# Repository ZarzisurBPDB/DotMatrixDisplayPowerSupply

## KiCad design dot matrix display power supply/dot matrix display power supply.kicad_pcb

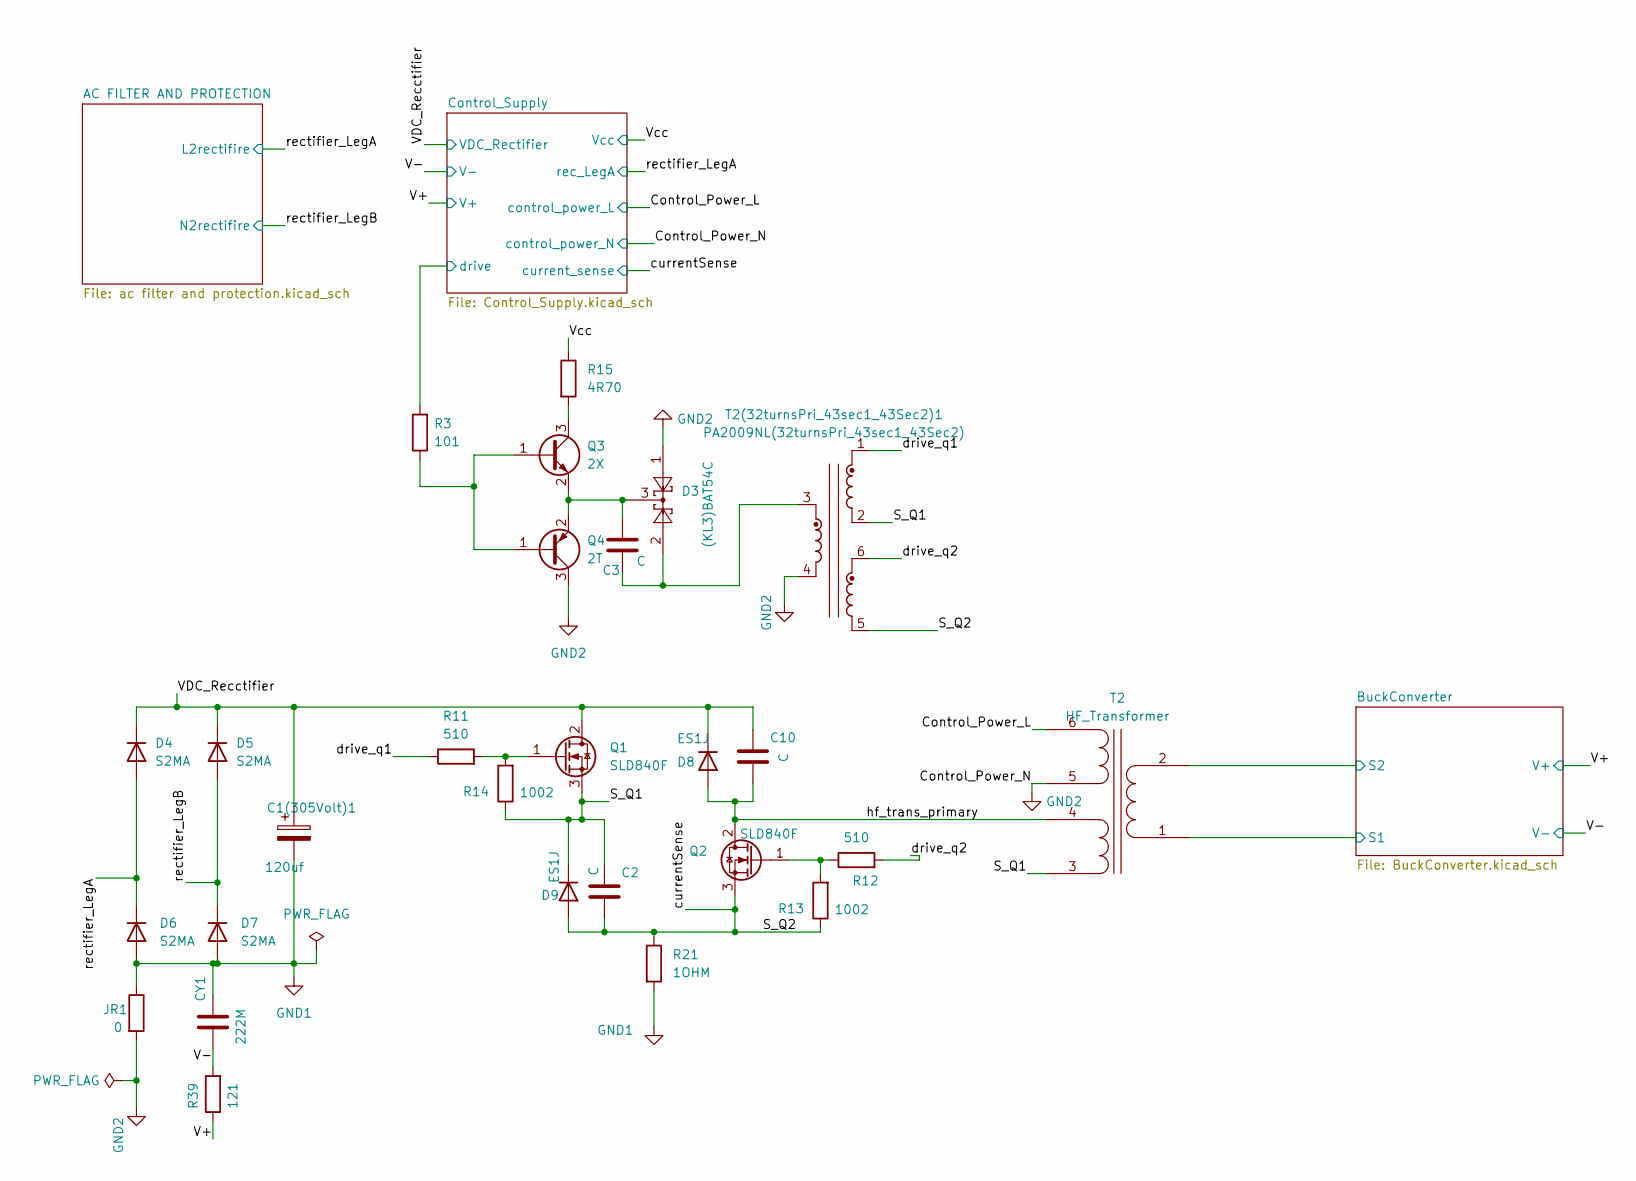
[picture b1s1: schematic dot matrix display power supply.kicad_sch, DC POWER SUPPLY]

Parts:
C1(305Volt)1: 120uf; CP_Radial_D16.0mm_P7.50mm
C2, C10: C; C_Disc_D4.7mm_W2.5mm_P5.00mm
C3: C; C_0201_0603Metric
CY1: 222M; C_Axial_L3.8mm_D2.6mm_P7.50mm_Horizontal
D3: (KL3)BAT54C; SOT-23
D4, D5, D6, D7: S2MA; D_SMA
D8, D9: ES1J; D_SMA
JR1: 0; R_0603_1608Metric
Q1, Q2: SLD840F; TO-252-2
Q3: 2X; SOT-23
Q4: 2T; SOT-23
R3: 101; R_0402_1005Metric
R11: 510; R_0402_1005Metric
R12: 510; R_0603_1608Metric
R13: 1002; R_0603_1608Metric
R14: 1002; R_0402_1005Metric
R15: 4R70; R_0603_1608Metric
R21: 1OHM; R_Axial_DIN0414_L11.9mm_D4.5mm_P15.24mm_Horizontal
R39: 121; R_0402_1005Metric
T2: HF_Transformer
T2(32turnsPri_43sec1_43Sec2)1: PA2009NL(32turnsPri_43sec1_43Sec2); Pulse_PA2004NL

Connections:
/BuckConverter/s1: T2.2 (s2); also elsewhere on the board
/BuckConverter/s2: T2.1 (s1); also elsewhere on the board
/Control_Power_L: T2.6 (controlPWR2); also elsewhere on the board
/Control_Supply/drive: R3.2; also elsewhere on the board
/S_Q1: C2.1, D9.1 (K), Q1.3 (S), R14.1, T2.3 (p1), T2(32turnsPri_43sec1_43Sec2)1.2
/S_Q2: C2.2, D9.2 (A), Q2.3 (S), R13.1, R21.1, T2(32turnsPri_43sec1_43Sec2)1.5; also elsewhere on the board
/V+: R39.1; also elsewhere on the board
/V-: CY1.2, R39.2; also elsewhere on the board
/VDC_Recctifier: C1(305Volt)1.1, C10.1, D4.1 (K), D5.1 (K), D8.1 (K), Q1.2 (D); also elsewhere on the board
/Vcc: R15.1; also elsewhere on the board
/drive_q1: R11.1, T2(32turnsPri_43sec1_43Sec2)1.1
/drive_q2: R12.2, T2(32turnsPri_43sec1_43Sec2)1.6
/hf_trans_primary: C10.2, D8.2 (A), Q2.2 (D), T2.4 (p2)
/rectifier_LegA: D4.2 (A), D6.1 (K); also elsewhere on the board
/rectifier_LegB: D5.2 (A), D7.1 (K); also elsewhere on the board
GND1: C1(305Volt)1.2, CY1.1, D6.2 (A), D7.2 (A), JR1.1, R21.2; also elsewhere on the board
GND2: D3.1, JR1.2, Q4.3 (C), T2.5 (ControlPWR1), T2(32turnsPri_43sec1_43Sec2)1.4; also elsewhere on the board
unnamed: C3.1, D3.2, T2(32turnsPri_43sec1_43Sec2)1.3
unnamed: Q1.1 (G), R11.2, R14.2
unnamed: Q2.1 (G), R12.1, R13.2
unnamed: Q3.1 (B), Q4.1 (B), R3.1
unnamed: Q3.3 (C), R15.2
unnamed: C3.2, D3.3, Q3.2 (E), Q4.2 (E)

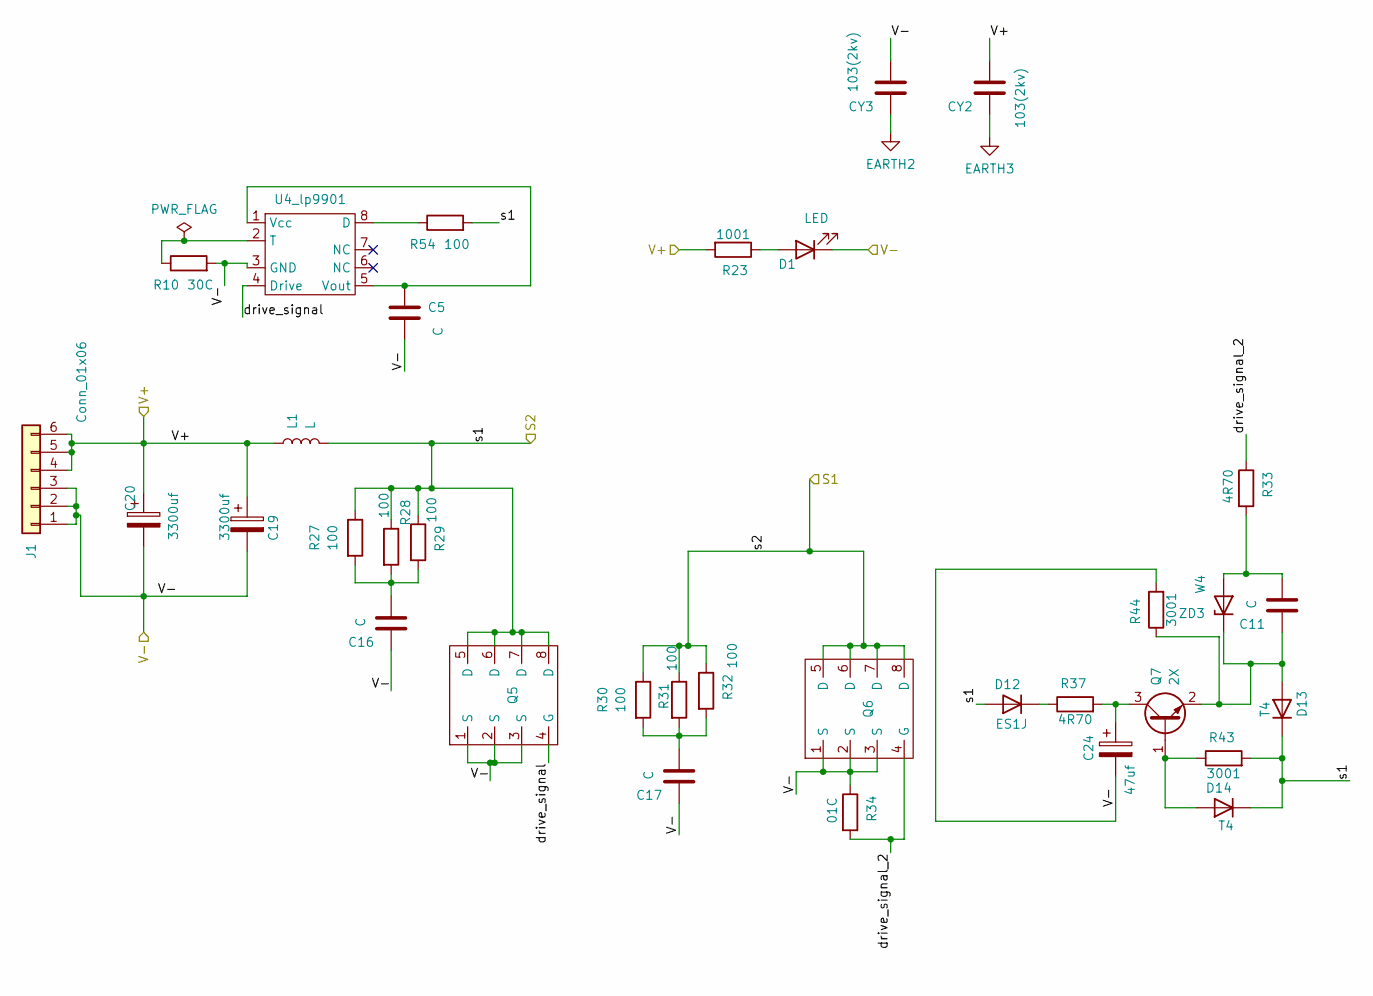
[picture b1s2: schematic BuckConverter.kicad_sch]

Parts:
C5, C11, C16, C17: C; C_01005_0402Metric
C19, C20: 3300uf; CP_Radial_D8.0mm_P5.00mm
C24: 47uf; CP_Radial_D5.0mm_P2.50mm
CY2, CY3: 103(2kv); C_Axial_L3.8mm_D2.6mm_P7.50mm_Horizontal
D1: LED; LED_D5.0mm
D12: ES1J; D_SMA
D13, D14: T4; D_SMA
J1: Conn_01x06; TerminalBlock_MaiXu_MX126-5.0-06P_1x06_P5.00mm
L1: L; L_Toroid_Horizontal_D22.4mm_P19.80mm_Vishay_TJ4
Q5, Q6: BSC022N03S
Q7: 2X; SOT-23
R10: 30C; R_0402_1005Metric
R23: 1001; R_0402_1005Metric
R27, R28, R29, R30, R31, R32, R54: 100; R_0402_1005Metric
R33, R37: 4R70; R_0402_1005Metric
R34: 01C; R_0402_1005Metric
R43, R44: 3001; R_0402_1005Metric
U4_lp9901: lp9901
ZD3: W4; D_SOD-523

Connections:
/BuckConverter/drive_signal: Q5.4 (G), U4_lp9901.4 (Drive)
/BuckConverter/drive_signal_2: Q6.4 (G), R33.1, R34.2
/BuckConverter/s1: D12.2 (A), D13.1 (K), D14.1 (K), L1.2, Q5.5 (D), Q5.6 (D), Q5.7 (D), Q5.8 (D), R27.1, R28.1, R29.1, R43.2, R54.2; also elsewhere on the board
/BuckConverter/s2: Q6.5 (D), Q6.6 (D), Q6.7 (D), Q6.8 (D), R30.1, R31.1, R32.1; also elsewhere on the board
/V+: C19.1, C20.1, CY2.2, J1.4, J1.5, J1.6, L1.1, R23.2; also elsewhere on the board
/V-: C5.1, C16.1, C17.1, C19.2, C20.2, C24.2, CY3.2, D1.1 (K), J1.1, J1.2, J1.3, Q5.1 (S), Q5.2 (S), Q5.3 (S), Q6.1 (S), Q6.2 (S), Q6.3 (S), R10.2, R34.1, R44.2, U4_lp9901.3 (GND); also elsewhere on the board
EARTH2: CY3.1
EARTH3: CY2.1
unnamed: C16.2, R27.2, R28.2, R29.2
unnamed: C17.2, R30.2, R31.2, R32.2
unnamed: D1.2 (A), R23.1
unnamed: D12.1 (K), R37.1
unnamed: C11.1, D13.2 (A), Q7.2 (E), R44.1, ZD3.1 (K)
unnamed: D14.2 (A), Q7.1 (B), R43.1
unnamed: C24.1, Q7.3 (C), R37.2
unnamed: R54.1, U4_lp9901.8 (D)
unnamed: R10.1, U4_lp9901.2 (T)
unnamed: C5.2, U4_lp9901.1 (Vcc), U4_lp9901.5 (Vout)
unnamed: C11.2, R33.2, ZD3.2 (A)

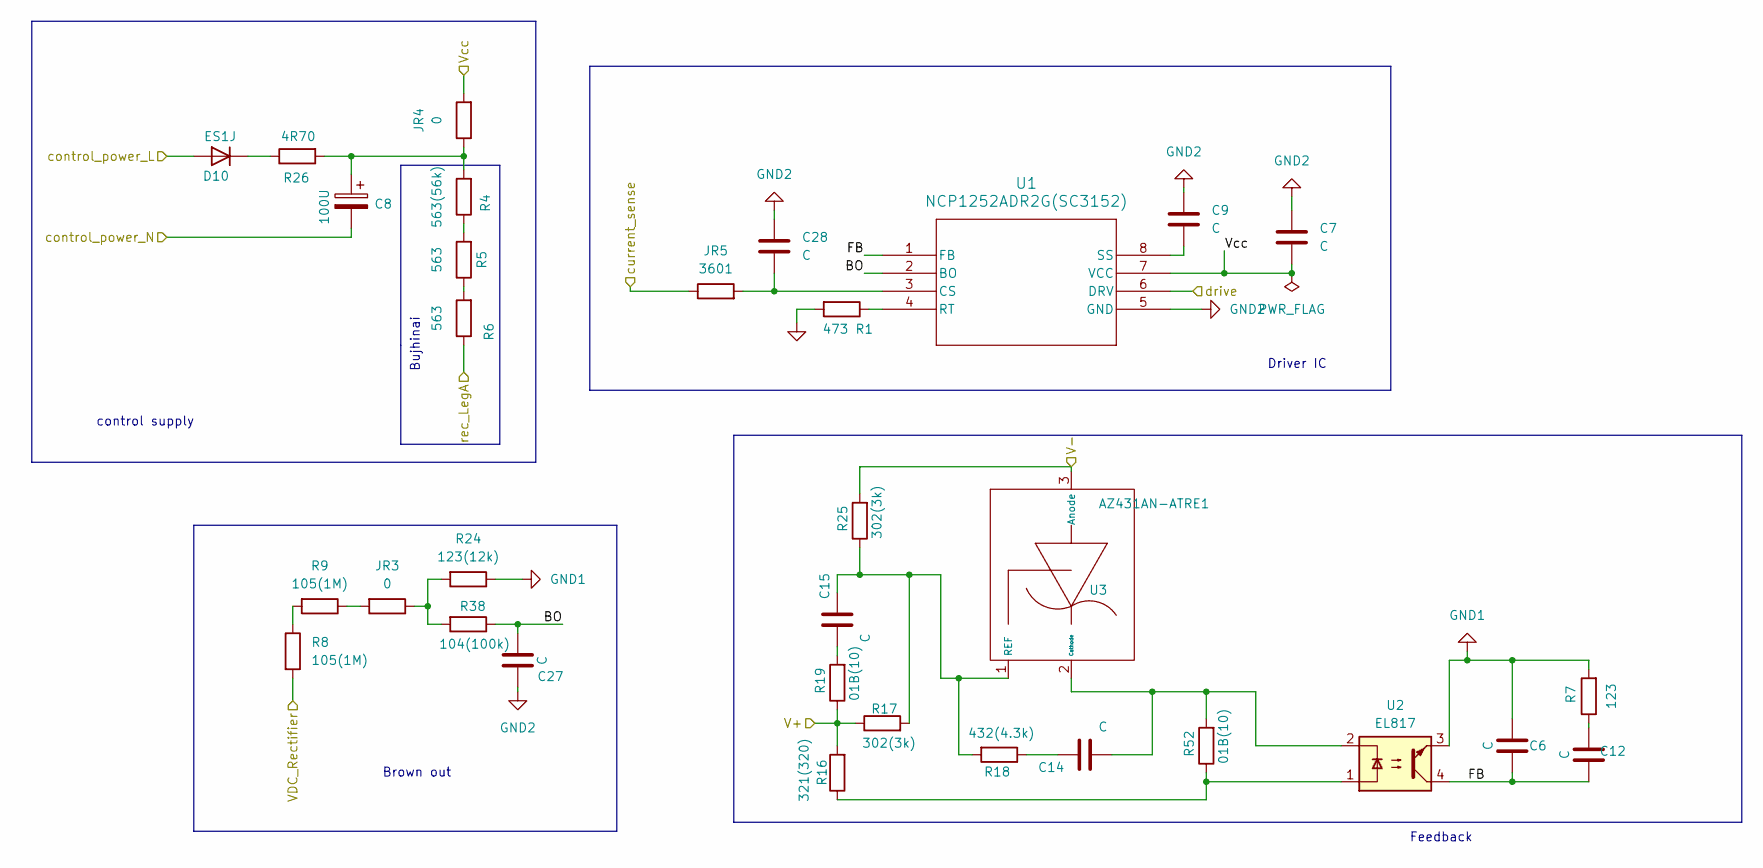
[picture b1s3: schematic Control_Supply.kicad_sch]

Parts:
C6, C7, C9, C12, C14, C15, C27, C28: C; C_01005_0402Metric
C8: 100U; CP_Radial_D5.0mm_P2.50mm
D10: ES1J; D_SMA
JR3, JR4: 0; R_0603_1608Metric
JR5: 3601; R_0603_1608Metric
R1: 473; R_0201_0603Metric
R4: 563(56k); R_0603_1608Metric
R5, R6: 563; R_0603_1608Metric
R7: 123; R_0201_0603Metric
R8, R9: 105(1M); R_0603_1608Metric
R16: 321(320); R_0402_1005Metric
R17, R25: 302(3k); R_0402_1005Metric
R18: 432(4.3k); R_0402_1005Metric
R19, R52: 01B(10); R_0402_1005Metric
R24: 123(12k); R_0201_0603Metric
R26: 4R70; R_0603_1608Metric
R38: 104(100k); R_0201_0603Metric
U1: NCP1252ADR2G(SC3152); SOIC8_ONS
U2: EL817; DIP-4_W7.62mm
U3: AZ431AN-ATRE1; EA1_az431

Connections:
/Control_Power_L: D10.2 (A); also elsewhere on the board
/Control_Supply/BO: C27.1, R38.1, U1.2 (BO)
/Control_Supply/FB: C6.1, C12.1, U1.1 (FB), U2.4
/Control_Supply/drive: U1.6 (DRV); also elsewhere on the board
/S_Q2: JR5.1; also elsewhere on the board
/V+: R16.2, R17.1, R19.1; also elsewhere on the board
/V-: R25.2, U3.3 (Anode); also elsewhere on the board
/VDC_Recctifier: R8.2; also elsewhere on the board
/Vcc: C7.2, JR4.2, U1.7 (VCC); also elsewhere on the board
/rectifier_LegA: R6.1; also elsewhere on the board
GND1: C6.2, R7.2, R24.1, U2.3; also elsewhere on the board
GND2: C7.1, C8.2, C9.1, C27.2, C28.1, R1.2, U1.5 (GND); also elsewhere on the board
unnamed: C8.1, JR4.1, R4.2, R26.2
unnamed: C12.2, R7.1
unnamed: C14.1, R18.1
unnamed: C15.2, R19.2
unnamed: D10.1 (K), R26.1
unnamed: JR3.1, R24.2, R38.2
unnamed: JR3.2, R9.1
unnamed: R4.1, R5.2
unnamed: R5.1, R6.2
unnamed: R8.1, R9.2
unnamed: R16.1, R52.1, U2.1
unnamed: C28.2, JR5.2, U1.3 (CS)
unnamed: R1.1, U1.4 (RT)
unnamed: C9.2, U1.8 (SS)
unnamed: C14.2, R52.2, U2.2, U3.2 (Cathode)
unnamed: C15.1, R17.2, R18.2, R25.1, U3.1 (REF)

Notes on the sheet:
Feedback
control supply
Brown out
Bujhinai
Driver IC

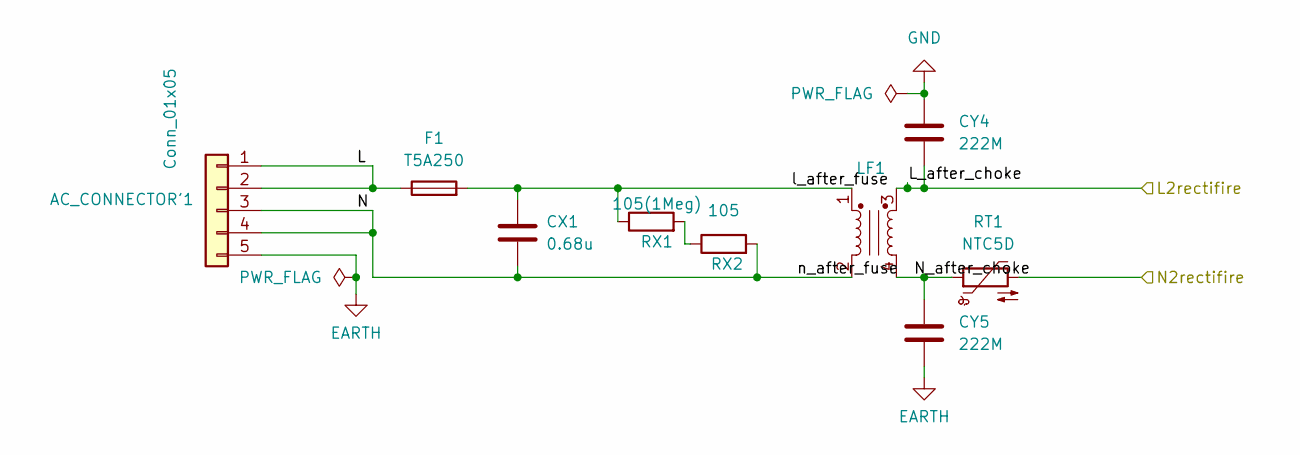
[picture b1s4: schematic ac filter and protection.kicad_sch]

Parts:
AC_CONNECTOR'1: Conn_01x05; TerminalBlock_MaiXu_MX126-5.0-05P_1x05_P5.00mm
CX1: 0.68u; C_Rect_L13.0mm_W5.0mm_P10.00mm_FKS3_FKP3_MKS4
CY4, CY5: 222M; C_Disc_D7.5mm_W5.0mm_P5.00mm
F1: T5A250; C_Disc_D4.3mm_W1.9mm_P5.00mm
LF1: Choke_Schaffner_RN102-0.3-02-12M; Choke_Schaffner_RN102-04-14.0x14.0mm
RT1: NTC5D; RV_Disc_D7mm_W3.4mm_P5mm
RX1: 105(1Meg); R_0603_1608Metric
RX2: 105; R_0603_1608Metric

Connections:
/AC FILTER AND PROTECTION/L: AC_CONNECTOR'1.1, AC_CONNECTOR'1.2, F1.1
/AC FILTER AND PROTECTION/N: AC_CONNECTOR'1.3, AC_CONNECTOR'1.4, CX1.2, LF1.2, RX2.2
/AC FILTER AND PROTECTION/N_after_choke: CY5.1, LF1.4, RT1.1
/AC FILTER AND PROTECTION/l_after_fuse: CX1.1, F1.2, LF1.1, RX1.1
/rectifier_LegA: CY4.2, LF1.3; also elsewhere on the board
/rectifier_LegB: RT1.2; also elsewhere on the board
EARTH: AC_CONNECTOR'1.5, CY5.2
GND: CY4.1
unnamed: RX1.2, RX2.1

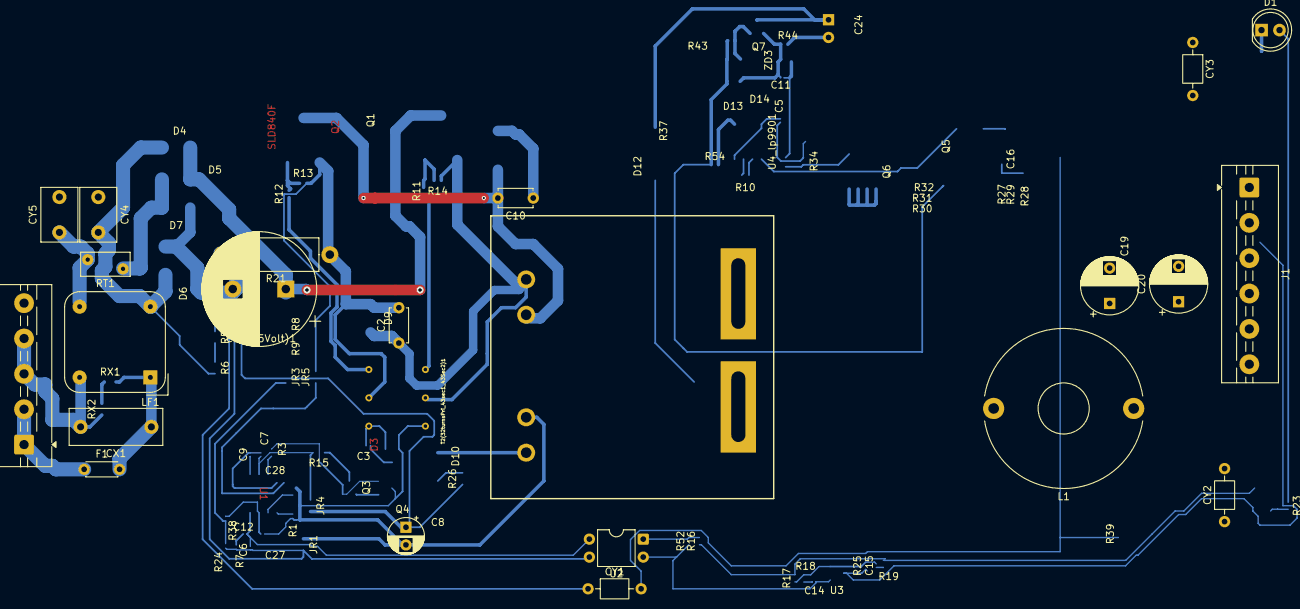
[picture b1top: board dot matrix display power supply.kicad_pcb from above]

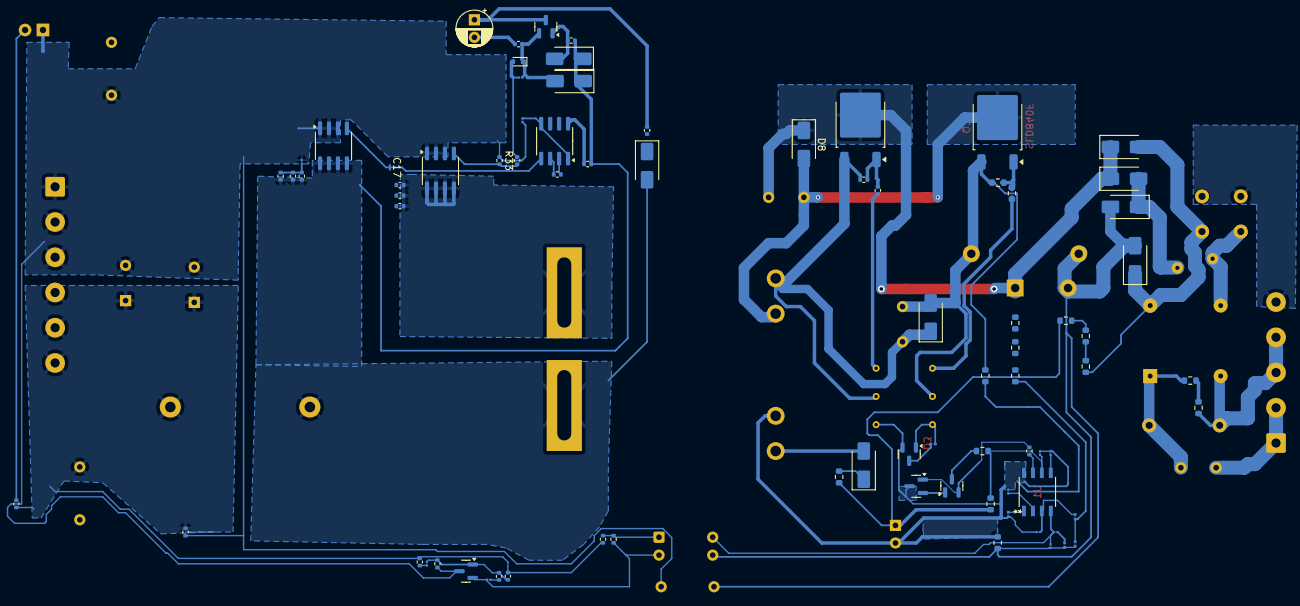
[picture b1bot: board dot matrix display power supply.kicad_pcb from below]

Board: 2 copper layers, 102 parts (80 on the bottom side), 60 nets.

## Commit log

2025-11-05 Initial commit of KiCad project
